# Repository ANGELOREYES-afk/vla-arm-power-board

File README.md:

# VLA arm power board

A 36 V regen brake and precharge board for a low-cost robot arm built to train vision-language-action (VLA) models. This repo has the KiCad project, the fabrication and assembly files, the arm's CAD, and the story of how the board came to be.

| | |
| --- | --- |
| **Supply** | 36 V, 27 A bench supply, XT60 input |
| **Loads** | three Unitree IM6014 actuators on XT30 outputs, 15 A each |
| **Board** | rev 3, 2 layers, 2 oz copper, 96.5 × 128 mm, 1.6 mm FR-4 |
| **Status** | ERC and DRC clean (including schematic parity). Ready to fabricate, not yet built. |

## The story

### The arm

The goal is a robot arm cheap enough that students and small labs can collect their own demonstrations and train VLA policies on them. Its first task is scooping ingredients into bowls, the kind of repetitive job fast-casual kitchens do all day.

The arm runs Unitree IM6014 actuators at 36 V over RS-485. LeRobot handles teleoperation and demo collection, and pi0.5 is the first policy. The current build has three joints with 3D-printed housings and carbon-fibre tube links. The joints move under control, the arm is simulated in Gazebo, and inverse kinematics is working. Simulink and LTspice models have been run for the controls and power electronics.

### What went wrong on the bench

Two problems pushed the project toward building its own power electronics.

1. **The USB to RS-485 adapter melted during testing.** A cheap, non-isolated adapter is the only thing between the computer and a motor bus that shares ground with a 27 A supply.
2. **A bench supply can source current but cannot sink it.** When the actuators brake hard they become generators and push energy back onto the 36 V bus. With nowhere to go, the bus voltage climbs, and the motor controllers' absolute limit is 44 V (moteus r4). On top of that, plugging a supply into 4000 µF of bulk capacitance sparks the connector every time.

This board fixes the second problem. An isolated RS-485 hub (next steps below) fixes the first.

### How the board works

```
PSU 36 V ─ XT60 ─ fuse ─ ideal diode ─┬─ main FET ──────────┬─ bus: 4000 µF ─ 3 × XT30 to motors
                                      └─ precharge FET+PTC ─┘          │
                                                                 brake chopper ─ 4.7 Ω 100 W resistor
```

- **Precharge.** At power-up a TI TPS48111-Q1 turns on a small FET that charges the bus through two 60 Ω PTCs in parallel (about 1.2 A at most). When the bus passes 60% of the supply, comparator U3B switches in the main CSD19536KTT FET, slew-limited to about 3 A into the capacitors. No spark.
- **Reverse blocking.** An LM5050-1 ideal-diode controller with a second CSD19536KTT stops regen current from flowing back into the supply.
- **Brake chopper.** A TL431 reference and LM393 comparator with hysteresis watch the bus. At 40.2–42.2 V (set by trimmer RV1) a UCC27517 drives an IRFB4110 that dumps energy into an off-board Arcol HS100 4.7 Ω 100 W resistor. It turns off about 2 V lower, so it cannot latch on at 36 V. An MUR1520 freewheels the resistor's inductance.
- **Protection and extras.** 25 A / 58 V MINI blade fuse, SMBJ43A on the input and SMCJ43A on the bus, a 12 V rail from an R-78HB12, a bus-voltage ADC output and a brake-active flag.

### What changed along the way

- **48 V to 36 V.** An early review offered a 48 V brake window (50.9–57.9 V) and it was picked up without checking against the real supply. That would never have fired before the controllers hit their 44 V limit. The window was moved to 40.2–42.2 V and the TVS diodes were changed to 43 V parts to match.
- **The fuse.** The first design used a 20 A fuse, which looked marginal against the motors' current spikes. With a 27 A supply, F1 became a 25 A part. It is a 58 V-rated MINI fuse, because common 32 V automotive blade fuses are under-rated for this bus.
- **Manufacturability pass (rev 3).** The design rules were raised from KiCad's defaults to JLCPCB's 2 oz limits, which caught XT30/XT60 support pads with 0.2 mm copper rings (now 0.3 mm). Thermal spokes on the connector ground pins were widened, the VBUS pour was widened and fed from a second side, copper was cleared under the mounting screws, and the silkscreen was labelled for assembly.
- **Precharge switch-over at 60%.** This is deliberate. The motors can draw about half an amp while the bus charges without stalling the PTCs. The trade-off is that the bus has to reach 60% before the main FET closes, so the motors should stay disabled until it is fully up.

### Still open

- The arm's real peak current has not been measured yet.
- XT30/XT60 polarity should be checked against the + marks on the physical housings before ordering.
- The TPS48111-Q1 orderable suffix should be confirmed with TI.
- Passives in the BOM are specified by value and rating, not by a particular manufacturer.

## Next steps

- **Isolated RS-485 hub.** USB-C into an FTDI FT4232H, then four isolated RS-485 ports with integrated isolated power (5 kV, rated 25 Mbps, enough for the IM6014's 6 Mbps mode). One port per joint, with TVS protection and switchable termination.
- **Load cell amplifier.** ADS1232 24-bit bridge ADC on an RP2040, weighing each scoop so the policy can be checked against a target portion.
- **CNC aluminium mounts.** The 19 printed joint plates, tube clamps and output hubs remade in 6061-T6. They're shown in aluminium below.

## Files

| Path | Contents |
| --- | --- |
| `hardware/` | KiCad 8 project (open `Untitled.kicad_pro`), with the project symbol and footprint library |
| `fab/regen-board-gerbers.zip` | Gerbers and drill files, ready to upload |
| `fab/regen-board-BOM.xlsx`, `.csv` | Bill of materials for full assembly (55 lines, 82 placements) |
| `fab/regen-board-CPL.csv` | Pick-and-place positions, all parts on the top side |
| `cad/arm-assembly.step` | Arm assembly from Onshape |
| `docs/images/` | Schematics, layout, renders and photos |

**Ordering notes:** 2 layers, 1.6 mm, 2 oz outer copper, HASL lead-free. The fuse insert (Littelfuse 0997025.WXN) and the off-board brake resistor are not placed by the assembler. J9 and J10 are solder pads for the resistor leads. The IRFB4110 brake FET needs a heatsink.

More about the project: [angeloreyes-afk.github.io/portfolio](https://angeloreyes-afk.github.io/portfolio/)

## License

The hardware design files are licensed under the [CERN Open Hardware Licence Version 2 – Strongly Reciprocal](LICENSE) (CERN-OHL-S-2.0). If you make or share a modified version, you must publish your modified design files under the same licence.

Source location: <https://github.com/ANGELOREYES-afk/vla-arm-power-board>

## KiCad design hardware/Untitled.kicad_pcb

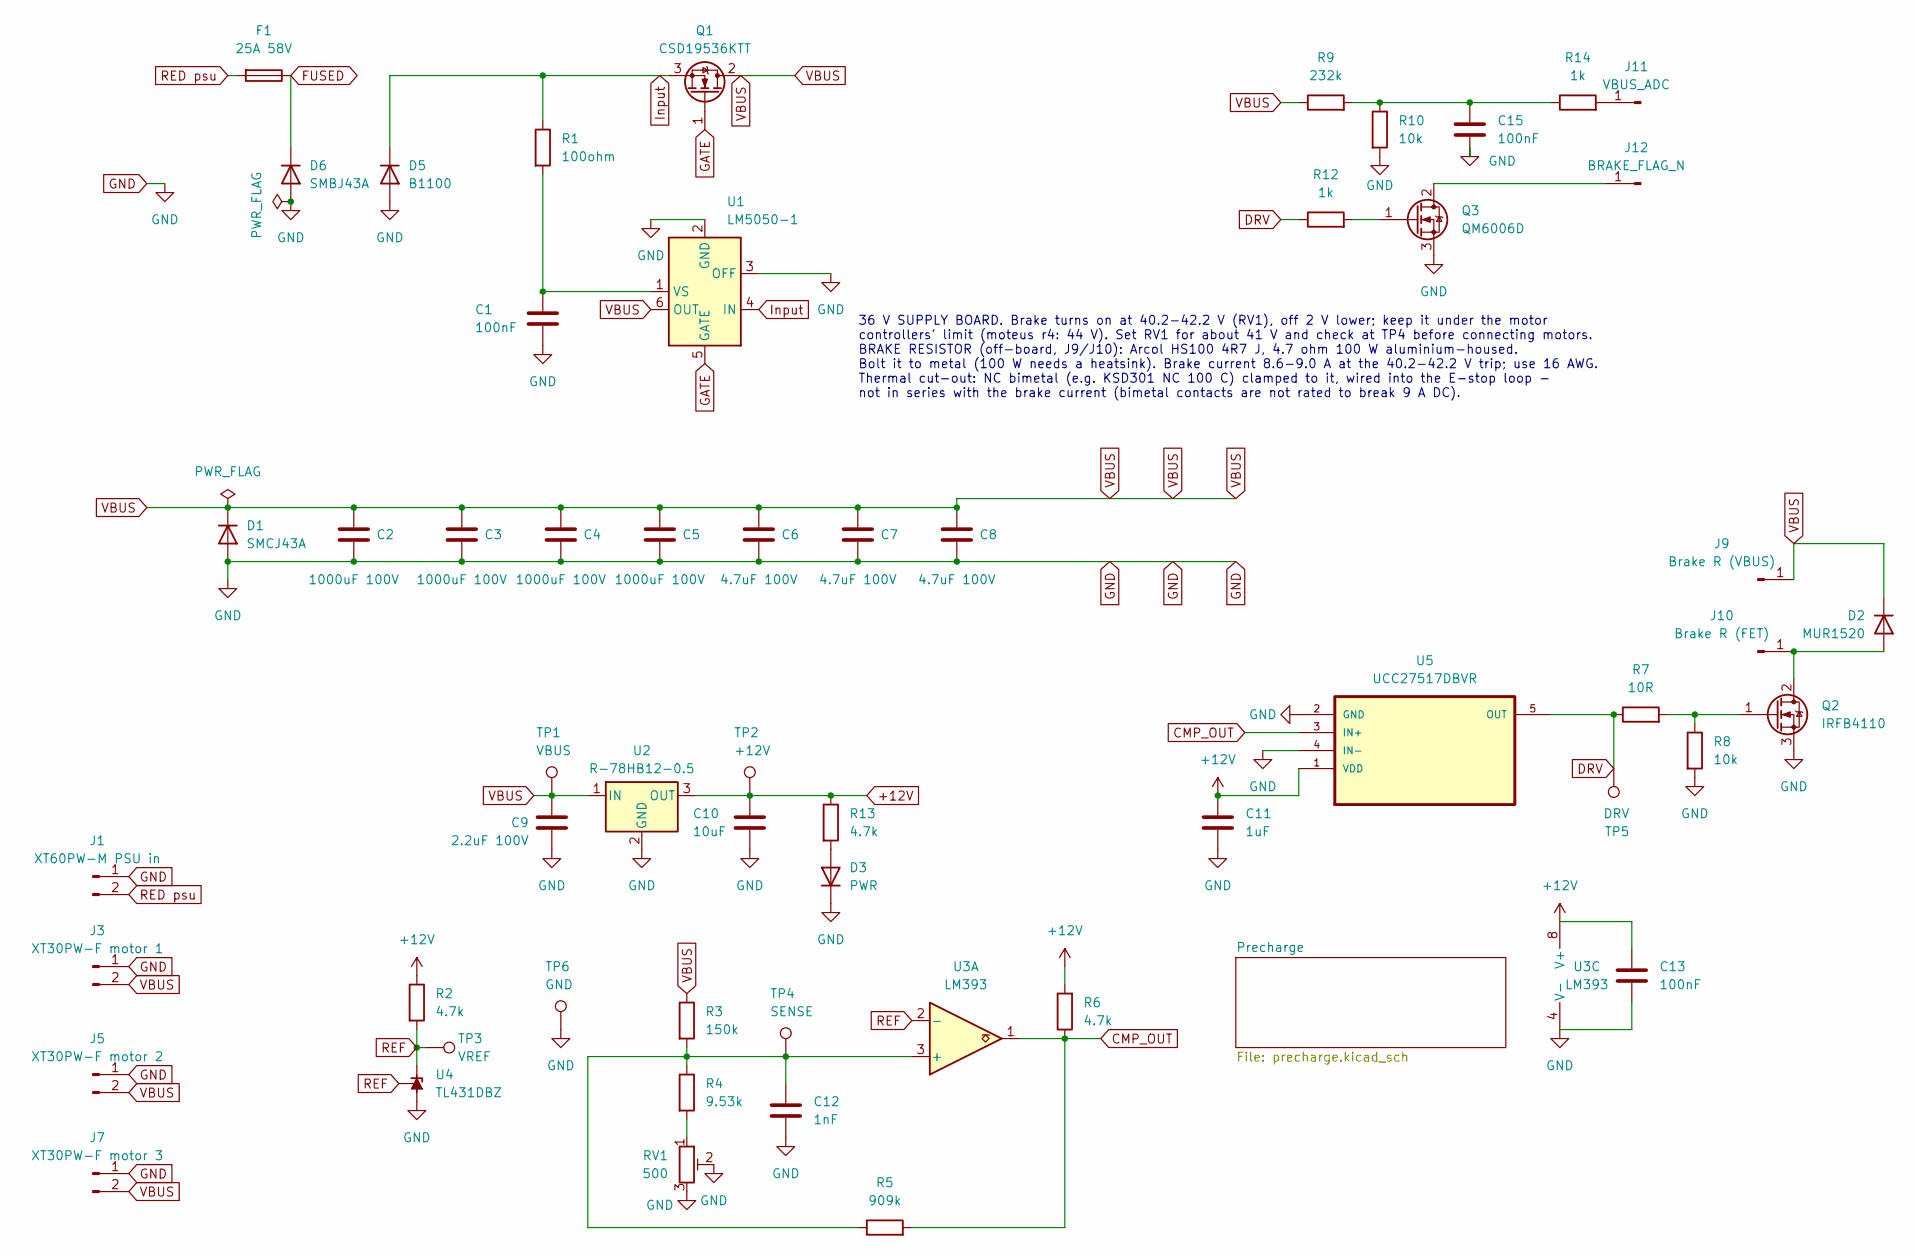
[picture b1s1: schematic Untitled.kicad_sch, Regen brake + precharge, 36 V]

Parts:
C1: 100nF; C_0805_2012Metric
C2, C3, C4, C5: 1000uF 100V; CP_Radial_D18.0mm_P7.50mm
C6, C7, C8: 4.7uF 100V; C_1210_3225Metric
C9: 2.2uF 100V; C_1210_3225Metric
C10: 10uF; C_0805_2012Metric
C11: 1uF; C_0603_1608Metric
C12: 1nF; C_0603_1608Metric
C13, C15: 100nF; C_0603_1608Metric
D1: SMCJ43A; D_SMC
D2: MUR1520; TO-220-2_Vertical; MPN MUR1520 (TO-220AC)
D3: PWR; LED_0603_1608Metric
D5: B1100; D_SMA
D6: SMBJ43A; D_SMB
F1: 25A 58V; Fuseholder_Blade_Mini_Keystone_3568; MPN Littelfuse 0997025.WXN (MINI 25A 58VDC)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
J1: XT60PW-M PSU in; AMASS_XT60PW-M_1x02_P7.20mm_Horizontal_D2.9mm
J3: XT30PW-F motor 1; AMASS_XT30PW-F_1x02_P2.50mm_Horizontal_SupportPad1.6mm
J5: XT30PW-F motor 2; AMASS_XT30PW-F_1x02_P2.50mm_Horizontal_SupportPad1.6mm
J7: XT30PW-F motor 3; AMASS_XT30PW-F_1x02_P2.50mm_Horizontal_SupportPad1.6mm
J9: Brake R (VBUS); SolderWire-1.5sqmm_1x01_D1.7mm_OD3mm
J10: Brake R (FET); SolderWire-1.5sqmm_1x01_D1.7mm_OD3mm
J11: VBUS_ADC; PinHeader_1x01_P2.54mm_Vertical
J12: BRAKE_FLAG_N; PinHeader_1x01_P2.54mm_Vertical
Q1: CSD19536KTT; TO-263-2; MPN TI CSD19536KTT
Q2: IRFB4110; TO-220-3_Vertical
Q3: QM6006D; TO-252-2
R1: 100ohm; R_0603_1608Metric
R2, R6, R13: 4.7k; R_0603_1608Metric
R3: 150k; R_0805_2012Metric
R4: 9.53k; R_0603_1608Metric
R5: 909k; R_0603_1608Metric
R7: 10R; R_0805_2012Metric
R8, R10: 10k; R_0603_1608Metric
R9: 232k; R_0805_2012Metric
R12, R14: 1k; R_0603_1608Metric
RV1: 500; Potentiometer_Bourns_3296W_Vertical; MPN Bourns 3296W-1-501LF
TP1: VBUS; TestPoint_Keystone_5000-5004_Miniature
TP2: +12V; TestPoint_Keystone_5000-5004_Miniature
TP3: VREF; TestPoint_Keystone_5000-5004_Miniature
TP4: SENSE; TestPoint_Keystone_5000-5004_Miniature
TP5: DRV; TestPoint_Keystone_5000-5004_Miniature
TP6: GND; TestPoint_Keystone_5000-5004_Miniature
U1: LM5050-1; TSOT-23-6
U2: R-78HB12-0.5; Converter_DCDC_RECOM_R-78HB-0.5_THT
U3: LM393; SOIC-8_3.9x4.9mm_P1.27mm
U4: TL431DBZ; SOT-23
U5: UCC27517DBVR; SOT-23-5

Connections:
+12V: C10.1, C11.1, C13.1, R2.1, R6.2, R13.1, TP2.1, U2.3 (OUT), U3.8 (V+), U5.1 (VDD); also elsewhere on the board
CMP_OUT: R5.2, R6.1, U3.1, U5.3 (IN+)
DRV: R7.1, R12.1, TP5.1, U5.5 (OUT)
FUSED: D6.1 (K), F1.1; also elsewhere on the board
GATE: Q1.1 (G), U1.5 (GATE)
GND: C1.2, C2.2, C3.2, C4.2, C5.2, C6.1, C7.1, C8.1, C9.2, C10.2, C11.2, C12.2, C13.2, C15.2, D1.2 (A), D3.1 (K), D5.2 (A), D6.2 (A), J1.1, J3.1, J5.1, J7.1, Q2.3 (S), Q3.3 (S), R8.2, R10.2, RV1.2, RV1.3, TP6.1, U1.2 (GND), U1.3 (OFF), U2.2 (GND), U3.4 (V-), U4.3 (A), U5.2 (GND), U5.4 (IN-); also elsewhere on the board
Input: D5.1 (K), Q1.3 (S), R1.1, U1.4 (IN); also elsewhere on the board
unnamed: C15.1, R9.2, R10.1, R14.1
unnamed: D2.2 (A), J10.1, Q2.2 (D)
unnamed: D3.2 (A), R13.2
unnamed: J11.1, R14.2
unnamed: J12.1, Q3.2 (D)
unnamed: Q2.1 (G), R7.2, R8.1
unnamed: Q3.1 (G), R12.2
unnamed: R4.2, RV1.1
unnamed: C1.1, R1.2, U1.1 (VS)
unnamed: C12.1, R3.2, R4.1, R5.1, TP4.1, U3.3 (+)
RED psu: F1.2, J1.2
REF: R2.2, TP3.1, U3.2 (-), U4.1 (K), U4.2 (REF)
VBUS: C2.1, C3.1, C4.1, C5.1, C6.2, C7.2, C8.2, C9.1, D1.1 (K), D2.1 (K), J3.2, J5.2, J7.2, J9.1, Q1.2 (D), R3.1, R9.1, TP1.1, U1.6 (OUT), U2.1 (IN); also elsewhere on the board

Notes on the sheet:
36 V SUPPLY BOARD. Brake turns on at 40.2-42.2 V (RV1), off 2 V lower; keep it under the motor controllers' limit (moteus r4: 44 V). Set RV1 for about 41 V and check at TP4 before connecting motors. BRAKE RESISTOR (off-board, J9/J10): Arcol HS100 4R7 J, 4.7 ohm 100 W aluminium-housed. Bolt it to me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

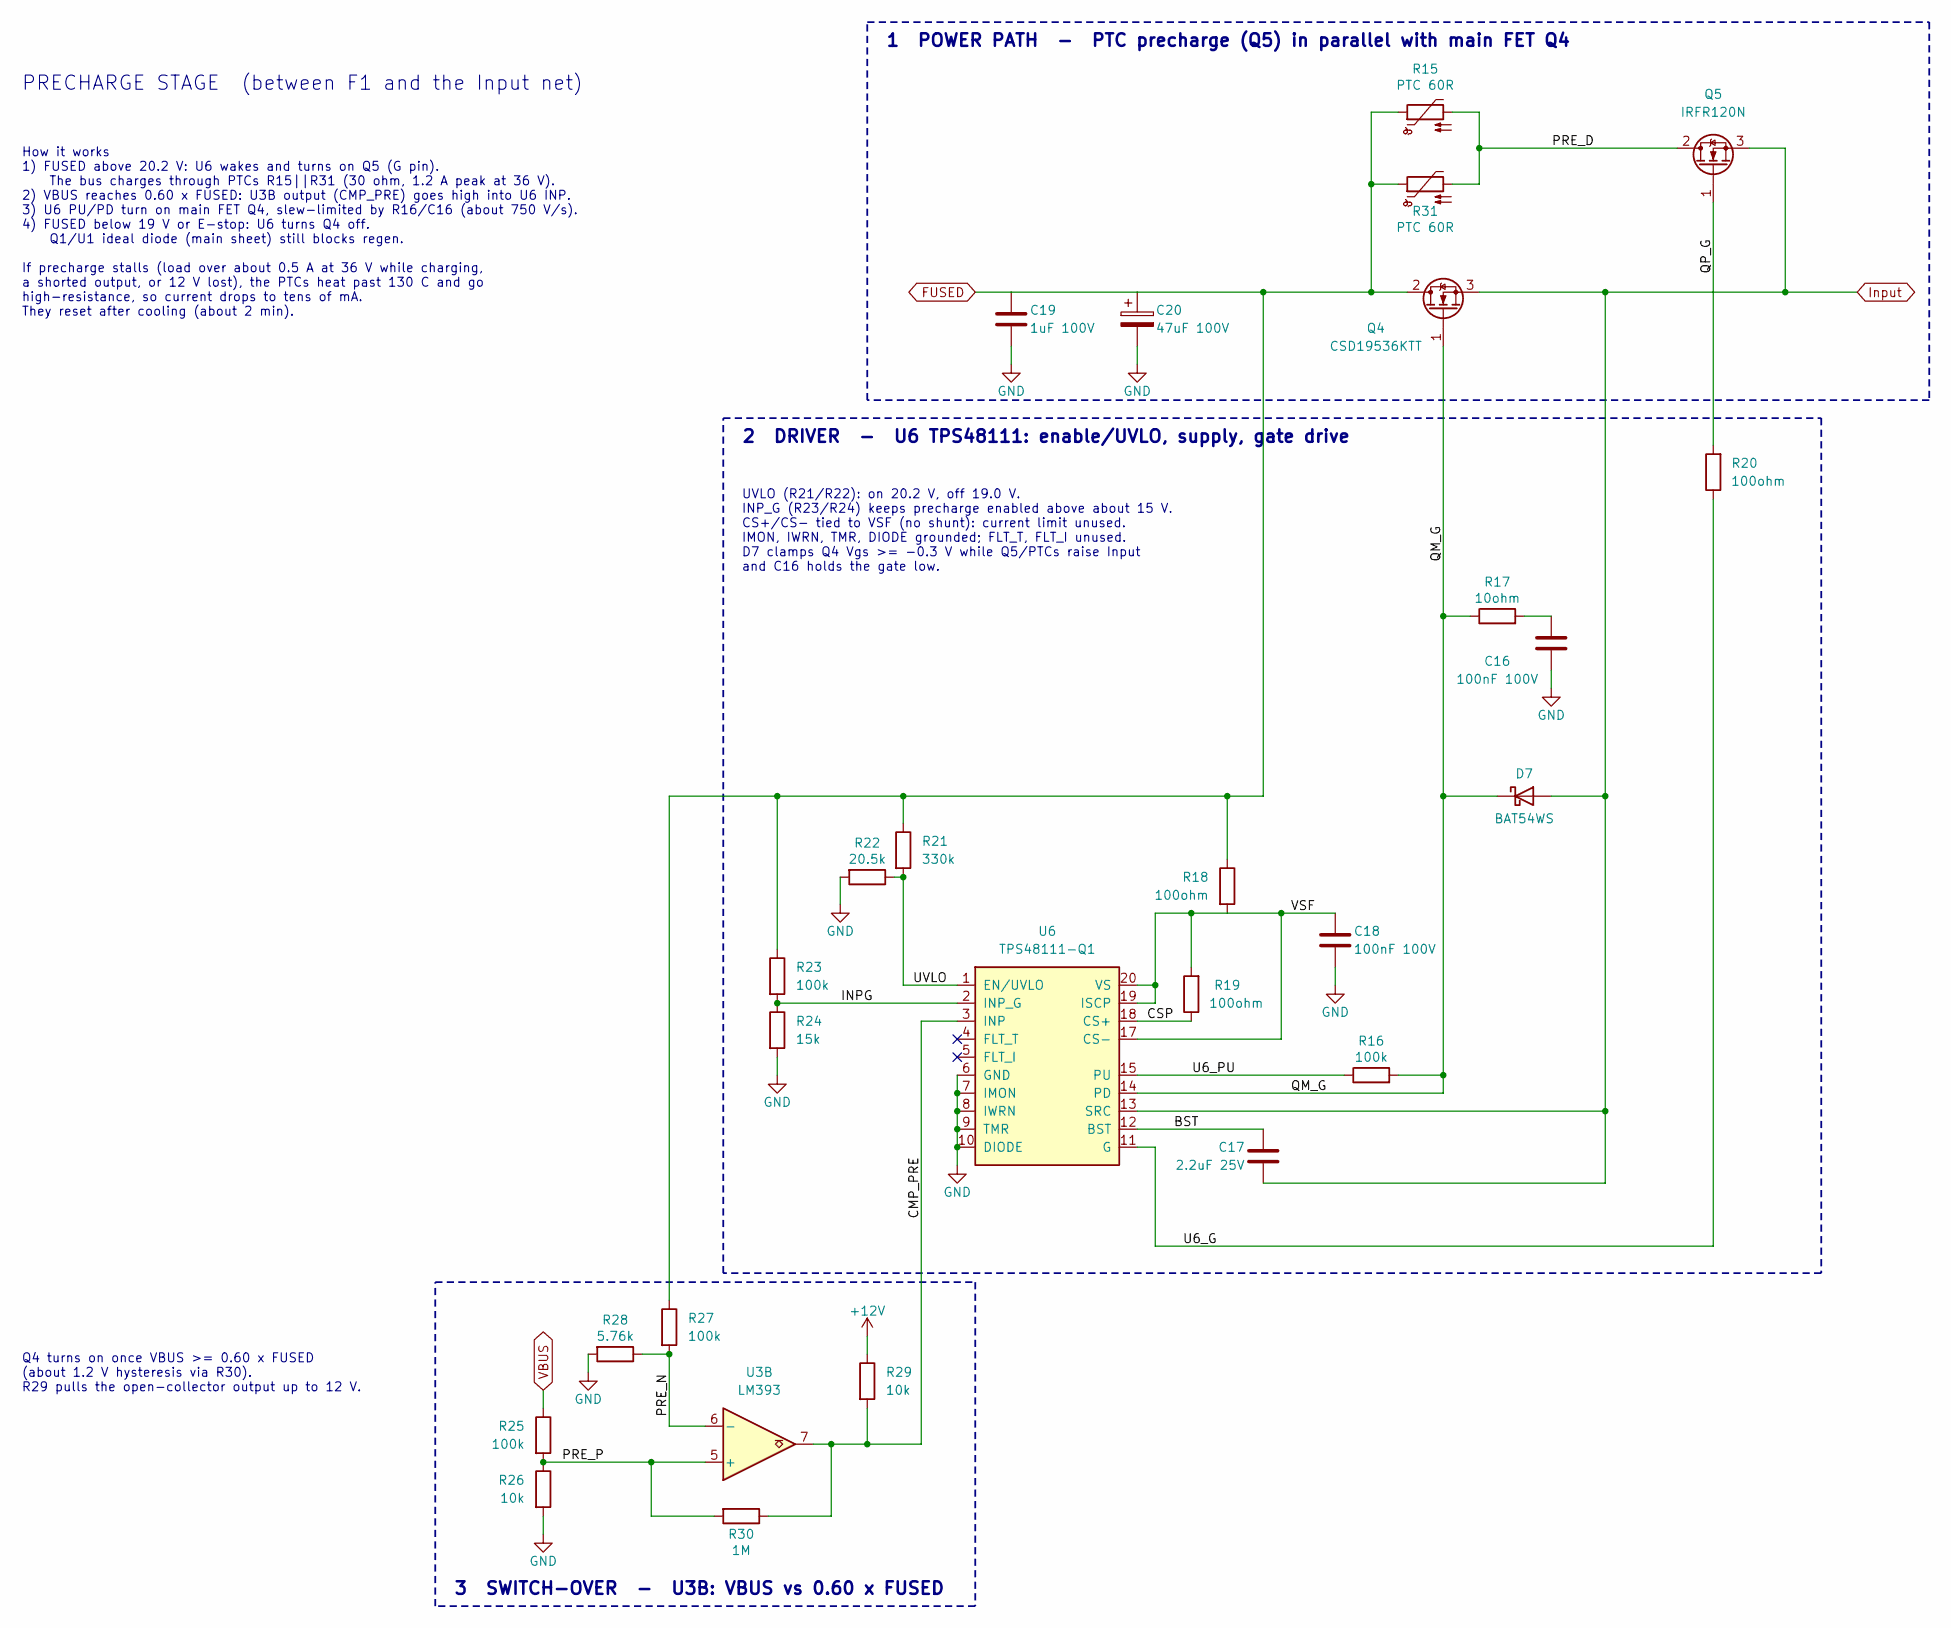
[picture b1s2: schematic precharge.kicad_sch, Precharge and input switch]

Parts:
C16, C18: 100nF 100V; C_0805_2012Metric
C17: 2.2uF 25V; C_0805_2012Metric
C19: 1uF 100V; C_1206_3216Metric
C20: 47uF 100V; CP_Radial_D10.0mm_P5.00mm
D7: BAT54WS; D_SOD-323; MPN Diodes Inc BAT54WS-7-F
Q4: CSD19536KTT; TO-263-2; MPN TI CSD19536KTT
Q5: IRFR120N; TO-252-2
R15, R31: PTC 60R; PTC_Disc_D13.5mm_T7mm_P5mm; MPN Vishay PTCEL13R600LBE (60 ohm PTC, 500 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
R16: 100k; R_0603_1608Metric
R17: 10ohm; R_0603_1608Metric
R18, R19, R20: 100ohm; R_0603_1608Metric
R21: 330k; R_0805_2012Metric
R22: 20.5k; R_0603_1608Metric
R23, R25, R27: 100k; R_0805_2012Metric
R24: 15k; R_0603_1608Metric
R26, R29: 10k; R_0603_1608Metric
R28: 5.76k; R_0603_1608Metric
R30: 1M; R_0603_1608Metric
U3: LM393; SOIC-8_3.9x4.9mm_P1.27mm
U6: TPS48111-Q1; TI_DGX0019A_VSSOP-19_3x5.1mm_P0.5mm

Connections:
+12V: R29.1; also elsewhere on the board
/Precharge/BST: C17.1, U6.12 (BST)
/Precharge/CMP_PRE: R29.2, R30.1, U3.7, U6.3 (INP)
/Precharge/CSP: R19.1, U6.18 (CS+)
/Precharge/INPG: R23.2, R24.1, U6.2 (INP_G)
/Precharge/PRE_D: Q5.2 (D), R15.2, R31.2
/Precharge/PRE_N: R27.2, R28.1, U3.6 (-)
/Precharge/PRE_P: R25.2, R26.1, R30.2, U3.5 (+)
/Precharge/QM_G: D7.1 (K), Q4.1 (G), R16.2, R17.1, U6.14 (PD)
/Precharge/QP_G: Q5.1 (G), R20.2
/Precharge/U6_G: R20.1, U6.11 (G)
/Precharge/U6_PU: R16.1, U6.15 (PU)
/Precharge/UVLO: R21.2, R22.1, U6.1 (EN/UVLO)
/Precharge/VSF: C18.1, R18.2, R19.2, U6.17 (CS-), U6.19 (ISCP), U6.20 (VS)
FUSED: C19.1, C20.1, Q4.2 (D), R15.1, R18.1, R21.1, R23.1, R27.1, R31.1; also elsewhere on the board
GND: C16.2, C18.2, C19.2, C20.2, R22.2, R24.2, R26.2, R28.2, U6.6 (GND), U6.7 (IMON), U6.8 (IWRN), U6.9 (TMR), U6.10 (DIODE); also elsewhere on the board
Input: C17.2, D7.2 (A), Q4.3 (S), Q5.3 (S), U6.13 (SRC); also elsewhere on the board
unnamed: C16.1, R17.2
VBUS: R25.1; also elsewhere on the board

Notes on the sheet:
2 DRIVER - U6 TPS48111: enable/UVLO, supply, gate drive
UVLO (R21/R22): on 20.2 V, off 19.0 V. INP_G (R23/R24) keeps precharge enabled above about 15 V. CS+/CS- tied to VSF (no shunt): current limit unused. IMON, IWRN, TMR, DIODE grounded; FLT_T, FLT_I unused. D7 clamps Q4 Vgs >= -0.3 V while Q5/PTCs raise Input and C16 holds the gate low.
3 SWITCH-OVER - U3B: VBUS vs 0.60 x FUSED
How it works 1) FUSED above 20.2 V: U6 wakes and turns on Q5 (G pin). The bus charges through PTCs R15||R31 (30 ohm, 1.2 A peak at 36 V). 2) VBUS reaches 0.60 x FUSED: U3B output (CMP_PRE) goes high into U6 INP. 3) U6 PU/PD turn on main FET Q4, slew-limited by R16/C16 (about 750 V/s). 4) FUSED belo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
Q4 turns on once VBUS >= 0.60 x FUSED (about 1.2 V hysteresis via R30). R29 pulls the open-collector output up to 12 V.
PRECHARGE STAGE (between F1 and the Input net)
1 POWER PATH - PTC precharge (Q5) in parallel with main FET Q4

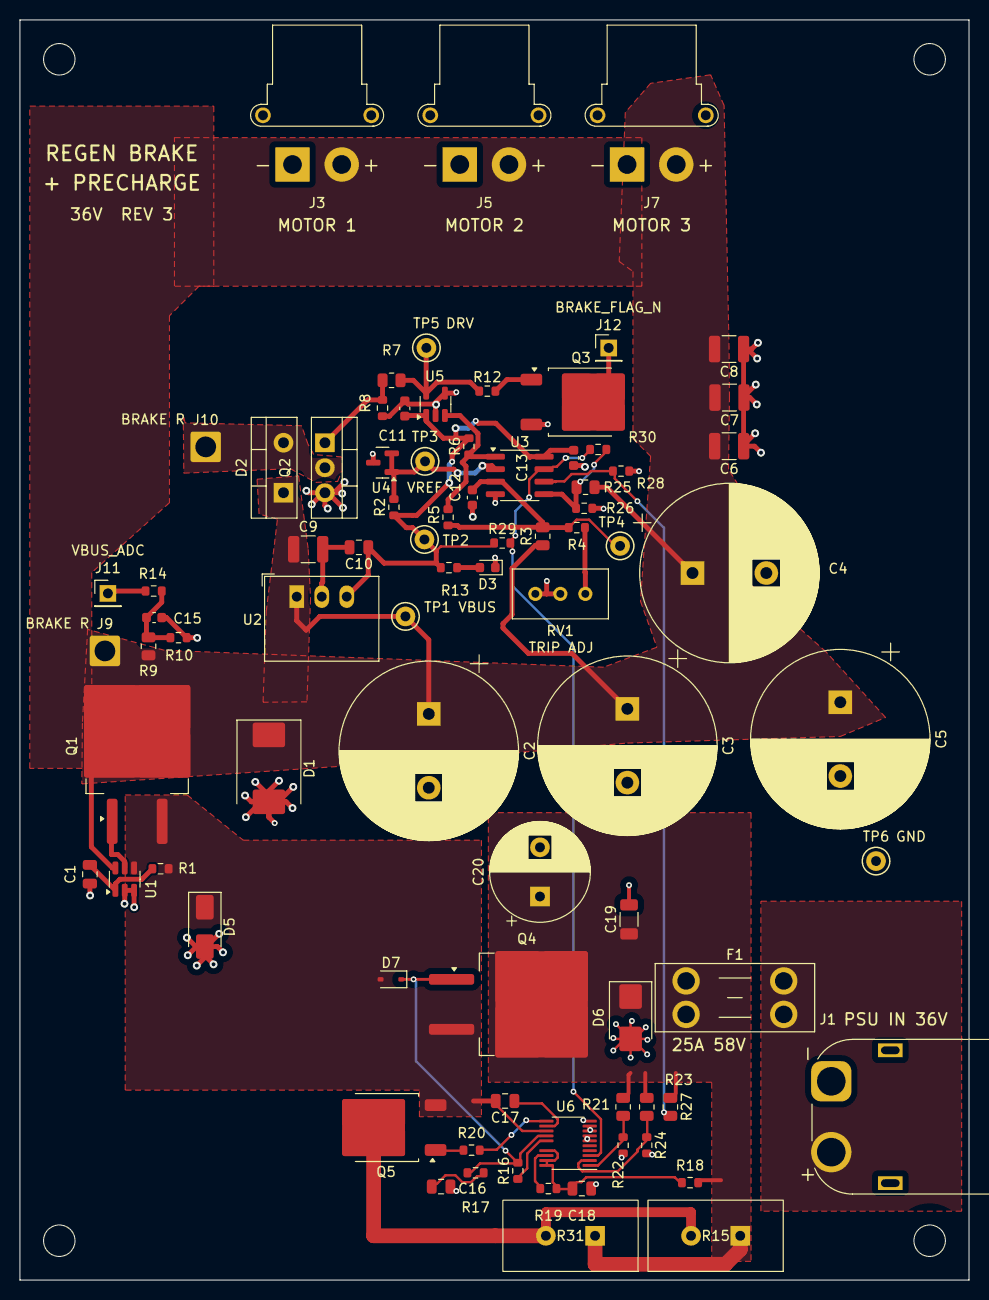
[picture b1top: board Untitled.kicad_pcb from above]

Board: 2 copper layers, 96.5 x 128.1 mm, 86 parts (0 on the bottom side), 34 nets.

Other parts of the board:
H1, H2, H3, H4: M3; MountingHole_3.2mm_M3

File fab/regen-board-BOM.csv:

Item,Designator,Qty,Value,Description,Manufacturer,Manufacturer part #,Package,Type,Notes
1,U1,1,LM5050-1,"High-side OR-ing FET controller, TSOT-23-6",Texas Instruments,LM5050MK-1/NOPB,TSOT-23-6,SMD,
2,U2,1,R-78HB12-0.5,"DC/DC 17-72 V in, 12 V 0.5 A out, SIP3",RECOM,R-78HB12-0.5,Converter_DCDC_RECOM_R-78HB-0.5_THT,THT,
3,U3,1,LM393,"Dual comparator, SOIC-8",Texas Instruments,LM393DR,SOIC-8_3.9x4.9mm_P1.27mm,SMD,
4,U4,1,TL431DBZ,"Adjustable shunt reference, SOT-23",Texas Instruments,TL431AIDBZR,SOT-23,SMD,
5,U5,1,UCC27517DBVR,"Low-side gate driver 4 A, SOT-23-5",Texas Instruments,UCC27517DBVR,SOT-23-5,SMD,
6,U6,1,TPS48111-Q1,"High-side driver with precharge, VSSOP-19 (DGX)",Texas Instruments,TPS48111LQDGXRQ1,TI_DGX0019A_VSSOP-19_3x5.1mm_P0.5mm,SMD,Confirm orderable suffix with TI
7,"Q1, Q4",2,CSD19536KTT,"N-MOSFET 100 V, 2.0 mOhm, D2PAK",Texas Instruments,CSD19536KTTT,TO-263-2,SMD,Main switch and ideal-diode FET
8,Q2,1,IRFB4110,"N-MOSFET 100 V 180 A, TO-220",Infineon,IRFB4110PBF,TO-220-3_Vertical,THT,Brake FET; mount on heatsink
9,Q3,1,QM6006D,"N-MOSFET 60 V 35 A, TO-252",UBIQ,QM6006D,TO-252-2,SMD,Brake flag open-drain
10,Q5,1,IRFR120N,"N-MOSFET 100 V 9.4 A, DPAK",Infineon,IRFR120NTRPBF,TO-252-2,SMD,Precharge FET
11,D1,1,SMCJ43A,"TVS diode, 43 V standoff, 1500 W, unidirectional",Littelfuse,SMCJ43A,D_SMC,SMD,
12,D2,1,MUR1520,"Ultrafast rectifier, 200 V 15 A, TO-220AC",onsemi,MUR1520G,TO-220-2_Vertical,THT,Brake freewheel diode
13,D3,1,PWR,LED green 0603,any,,0603,SMD,Power indicator
14,D5,1,B1100,"Schottky diode, 100 V 1 A",Diodes Inc,B1100-13-F,D_SMA,SMD,
15,D6,1,SMBJ43A,"TVS diode, 43 V standoff, 600 W, unidirectional",Littelfuse,SMBJ43A,D_SMB,SMD,
16,D7,1,BAT54WS,"Schottky diode, 30 V 200 mA",Diodes Inc,BAT54WS-7-F,D_SOD-323,SMD,
17,F1,1,25A 58V,"MINI blade fuse holder, PCB mount, 30 A",Keystone,3568,Fuseholder_Blade_Mini_Keystone_3568,THT,Fuse ordered separately: Littelfuse 0997025.WXN (25 A 58 VDC MINI)
18,J1,1,XT60PW-M  PSU in,"XT60 male, right-angle PCB mount",AMASS,XT60PW-M,AMASS_XT60PW-M_1x02_P7.20mm_Horizontal_D2.9mm,THT,
19,"J3, J5, J7",3,XT30PW-F,"XT30 female, right-angle PCB mount",AMASS,XT30PW-F,AMASS_XT30PW-F_1x02_P2.50mm_Horizontal_SupportPad1.6mm,THT,
20,J9,1,Brake R (VBUS),Solder pad for brake-resistor lead (no part),-,,SolderWire-1.5sqmm_1x01_D1.7mm_OD3mm,THT,Do not place: wire soldered at install
21,J10,1,Brake R (FET),Solder pad for brake-resistor lead (no part),-,,SolderWire-1.5sqmm_1x01_D1.7mm_OD3mm,THT,Do not place: wire soldered at install
22,J11,1,VBUS_ADC,1-pin header 2.54 mm,any,,PinHeader_1x01_P2.54mm_Vertical,THT,
23,J12,1,BRAKE_FLAG_N,1-pin header 2.54 mm,any,,PinHeader_1x01_P2.54mm_Vertical,THT,
24,C1,1,100nF,"Ceramic capacitor 100nF, 100 V (sits on the 36 V bus), X7R, 0805",any,,0805,SMD,
25,"C2, C3, C4, C5",4,1000uF 100V,"Aluminium electrolytic 1000uF 100V, low ESR, 18.0 mm dia, 7.50 mm pitch, 105 °C",any,,CP_Radial_D18.0mm_P7.50mm,THT,
26,"C6, C7, C8",3,4.7uF 100V,"Ceramic capacitor 4.7uF, 100 V, X7R, 1210",any,,1210,SMD,
27,C9,1,2.2uF 100V,"Ceramic capacitor 2.2uF, 100 V, X7R, 1210",any,,1210,SMD,
28,C10,1,10uF,"Ceramic capacitor 10uF, 25 V, X7R, 0805",any,,0805,SMD,
29,C11,1,1uF,"Ceramic capacitor 1uF, 25 V, X7R, 0603",any,,0603,SMD,
30,C12,1,1nF,"Ceramic capacitor 1nF, 50 V, X7R, 0603",any,,0603,SMD,
31,"C13, C15",2,100nF,"Ceramic capacitor 100nF, 25 V, X7R, 0603",any,,0603,SMD,
32,"C16, C18",2,100nF 100V,"Ceramic capacitor 100nF, 100 V, X7R, 0805",any,,0805,SMD,
33,C17,1,2.2uF 25V,"Ceramic capacitor 2.2uF, 25 V, X7R, 0805",any,,0805,SMD,
34,C19,1,1uF 100V,"Ceramic capacitor 1uF, 100 V, X7R, 1206",any,,1206,SMD,
35,C20,1,47uF 100V,"Aluminium electrolytic 47uF 100V, low ESR, 10.0 mm dia, 5.00 mm pitch, 105 °C",any,,CP_Radial_D10.0mm_P5.00mm,THT,
36,"R1, R18, R19, R20",4,100ohm,"Thick-film resistor 100ohm, 1%, 0.1 W, 0603",any,,0603,SMD,
37,"R2, R6, R13",3,4.7k,"Thick-film resistor 4.7k, 1%, 0.1 W, 0603",any,,0603,SMD,
38,R3,1,150k,"Thick-film resistor 150k, 1%, 0.125 W, 0805",any,,0805,SMD,
39,R4,1,9.53k,"Thick-film resistor 9.53k, 1%, 0.1 W, 0603",any,,0603,SMD,
40,R5,1,909k,"Thick-film resistor 909k, 1%, 0.1 W, 0603",any,,0603,SMD,
41,R7,1,10R,"Thick-film resistor 10R, 1%, 0.125 W, 0805",any,,0805,SMD,
42,"R8, R10, R26, R29",4,10k,"Thick-film resistor 10k, 1%, 0.1 W, 0603",any,,0603,SMD,
43,R9,1,232k,"Thick-film resistor 232k, 1%, 0.125 W, 0805",any,,0805,SMD,
44,"R12, R14",2,1k,"Thick-film resistor 1k, 1%, 0.1 W, 0603",any,,0603,SMD,
45,"R15, R31",2,PTC 60R,"PTC thermistor 60 Ohm, 500 VDC, 150 J",Vishay,PTCEL13R600LBE,PTC_Disc_D13.5mm_T7mm_P5mm,THT,Precharge resistors
46,R16,1,100k,"Thick-film resistor 100k, 1%, 0.1 W, 0603",any,,0603,SMD,
47,R17,1,10ohm,"Thick-film resistor 10ohm, 1%, 0.1 W, 0603",any,,0603,SMD,
48,R21,1,330k,"Thick-film resistor 330k, 1%, 0.125 W, 0805",any,,0805,SMD,
49,R22,1,20.5k,"Thick-film resistor 20.5k, 1%, 0.1 W, 0603",any,,0603,SMD,
50,"R23, R25, R27",3,100k,"Thick-film resistor 100k, 1%, 0.125 W, 0805",any,,0805,SMD,
51,R24,1,15k,"Thick-film resistor 15k, 1%, 0.1 W, 0603",any,,0603,SMD,
52,R28,1,5.76k,"Thick-film resistor 5.76k, 1%, 0.1 W, 0603",any,,0603,SMD,
53,R30,1,1M,"Thick-film resistor 1M, 1%, 0.1 W, 0603",any,,0603,SMD,
54,RV1,1,500,"Trimmer 500 Ohm, 25-turn, top adjust",Bourns,3296W-1-501LF,Potentiometer_Bourns_3296W_Vertical,THT,Sets brake threshold
55,"TP1, TP2, TP3, TP4, TP5, TP6",6,5001,Miniature PC test point,Keystone,5001,TestPoint_Keystone_5000-5004_Miniature,THT,
